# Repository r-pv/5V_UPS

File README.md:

# 5V_UPS

A real 5V Uninterruptible Power Supply (UPS) based on the [MP2637](https://www.monolithicpower.com/en/mp2637.html) IC, supporting 4.2V and 4.35V LiION/LiPO batteries. The design it's practically the design layout recomended by the manufacturer just with a few minor differences.

The board it's 30x30mm and it's capable of 2.5A battery charge and 2.4A boost output.

## Working as a proper UPS:

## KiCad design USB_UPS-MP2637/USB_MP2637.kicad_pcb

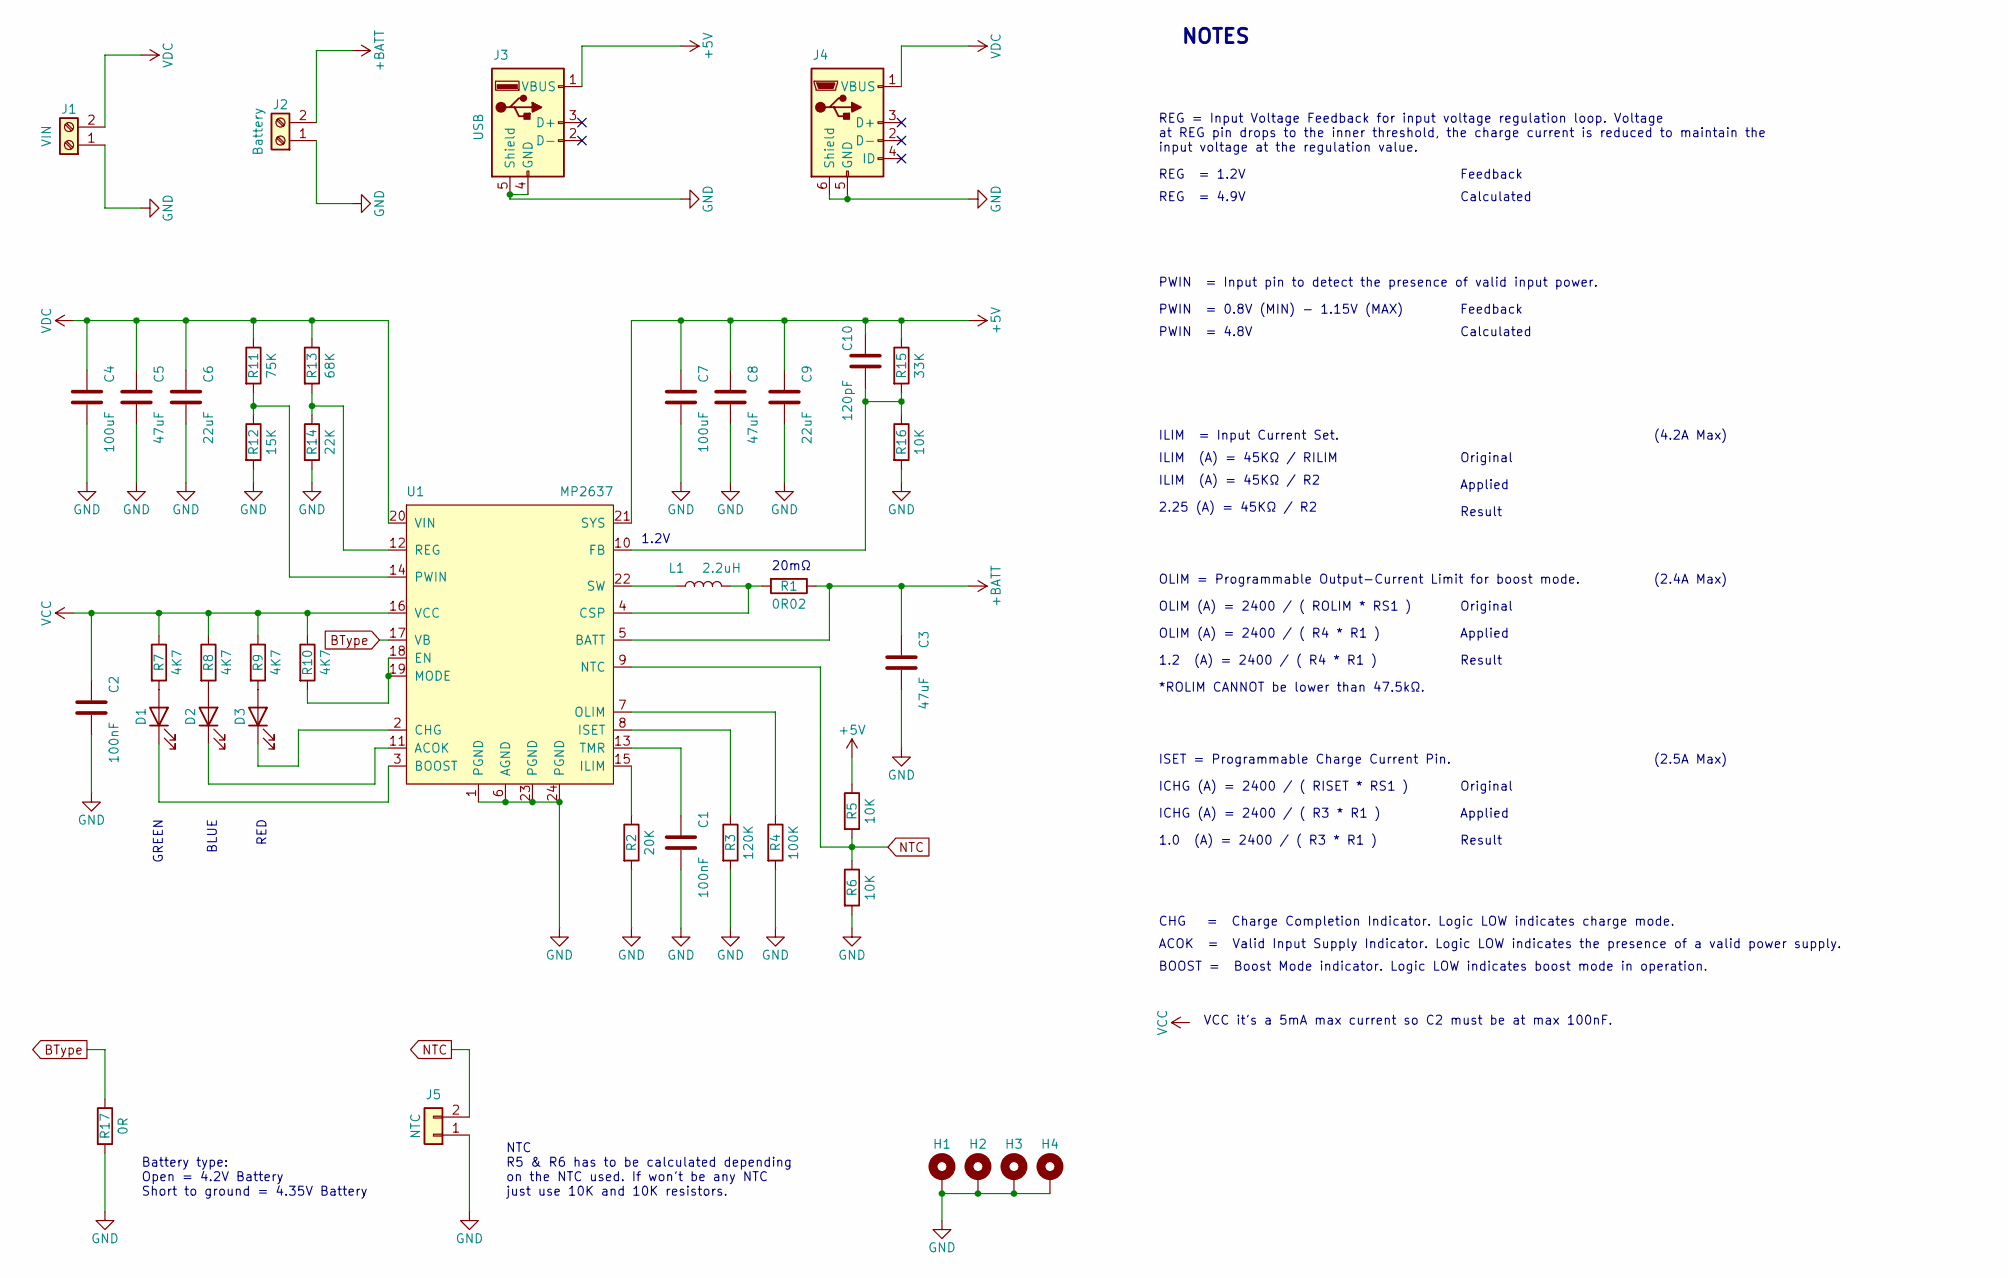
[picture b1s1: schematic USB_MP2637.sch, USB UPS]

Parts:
C1, C2: 100nF; C_0402_1005Metric
C3, C5, C8: 47uF; C_0805_2012Metric
C4, C7: 100uF; C_1210_3225Metric
C6, C9: 22uF; C_0805_2012Metric
C10: 120pF; C_0402_1005Metric
D1, D2, D3: LED_0603_1608Metric
H1, H2, H3, H4: MountingHole_2.2mm_M2_DIN965_Pad
J1: VIN; PinHeader_1x02_P2.54mm_Vertical
J2: Battery; PinHeader_1x02_P2.54mm_Vertical
J3: USB; USB_A_Molex_67643_Horizontal
J4: USB_Micro-B_Molex_47346-0001
J5: NTC; R_0805_2012Metric
L1: 2.2uH; Inductor-0603
R1: 0R02; R_1210_3225Metric
R2: 20K; R_0402_1005Metric
R3: 120K; R_0402_1005Metric
R4: 100K; R_0402_1005Metric
R5, R6, R16: 10K; R_0402_1005Metric
R7, R8, R9, R10: 4K7; R_0402_1005Metric
R11: 75K; R_0402_1005Metric
R12: 15K; R_0402_1005Metric
R13: 68K; R_0402_1005Metric
R14: 22K; R_0402_1005Metric
R15: 33K; R_0402_1005Metric
R17: 0R; R_0402_1005Metric
U1: MP2637; QFN-24_4x4mm-MP

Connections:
+5V: C7.1, C8.1, C9.1, C10.1, J3.1 (VBUS), R5.1, R15.1, U1.21 (SYS)
+BATT: C3.1, J2.2, R1.1, U1.5 (BATT)
BType: R17.1, U1.17 (VB)
GND: C1.2, C2.2, C3.2, C4.2, C5.2, C6.2, C7.2, C8.2, C9.2, H1.1, H2.1, H3.1, H4.1, J1.1, J2.1, J3.4 (GND), J3.5 (Shield), J4.5 (GND), J4.6 (Shield), J5.1, R2.2, R3.2, R4.2, R6.2, R12.2, R14.2, R16.2, R17.2, U1.1 (PGND), U1.6 (AGND), U1.23 (PGND), U1.24 (PGND)
NTC: J5.2, R5.2, R6.1, U1.9 (NTC)
unnamed: C1.1, U1.13 (TMR)
unnamed: C10.2, R15.2, R16.1, U1.10 (FB)
unnamed: D1.1 (K), U1.3 (BOOST)
unnamed: D1.2 (A), R7.2
unnamed: D2.1 (K), U1.11 (ACOK)
unnamed: D2.2 (A), R8.2
unnamed: D3.1 (K), U1.2 (CHG)
unnamed: D3.2 (A), R9.2
unnamed: L1.1, U1.22 (SW)
unnamed: L1.2, R1.2, U1.4 (CSP)
unnamed: R2.1, U1.15 (ILIM)
unnamed: R3.1, U1.8 (ISET)
unnamed: R4.1, U1.7 (OLIM)
unnamed: R10.2, U1.18 (EN), U1.19 (MODE)
unnamed: R11.2, R12.1, U1.14 (PWIN)
unnamed: R13.2, R14.1, U1.12 (REG)
VCC: C2.1, R7.1, R8.1, R9.1, R10.1, U1.16 (VCC)
VDC: C4.1, C5.1, C6.1, J1.2, J4.1 (VBUS), R11.1, R13.1, U1.20 (VIN)

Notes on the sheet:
OLIM (A) = 2400 / ( ROLIM * RS1 )
ICHG (A) = 2400 / ( RISET * RS1 )
ILIM (A) = 45KΩ / RILIM
1.2V
ILIM = Input Current Set.
OLIM = Programmable Output-Current Limit for boost mode.
ISET = Programmable Charge Current Pin.
ICHG (A) = 2400 / ( R3 * R1 )
1.0 (A) = 2400 / ( R3 * R1 )
Original
Applied
Result
OLIM (A) = 2400 / ( R4 * R1 )
1.2 (A) = 2400 / ( R4 * R1 )
ILIM (A) = 45KΩ / R2
2.25 (A) = 45KΩ / R2
REG = 1.2V
REG = Input Voltage Feedback for input voltage regulation loop. Voltage at REG pin drops to the inner threshold, the charge current is reduced to maintain the input voltage at the regulation value.
PWIN = Input pin to detect the presence of valid input power.
REG = 4.9V
Feedback
Calculated
PWIN = 0.8V (MIN) - 1.15V (MAX)
PWIN = 4.8V
*ROLIM CANNOT be lower than 47.5kΩ.
CHG = Charge Completion Indicator. Logic LOW indicates charge mode.
RED
BLUE
GREEN
ACOK = Valid Input Supply Indicator. Logic LOW indicates the presence of a valid power supply.
BOOST = Boost Mode indicator. Logic LOW indicates boost mode in operation.
NOTES
Battery type: Open = 4.2V Battery Short to ground = 4.35V Battery
(2.5A Max)
(2.4A Max)
(4.2A Max)
20mΩ
NTC R5 & R6 has to be calculated depending on the NTC used. If won't be any NTC just use 10K and 10K resistors.
VCC it's a 5mA max current so C2 must be at max 100nF.

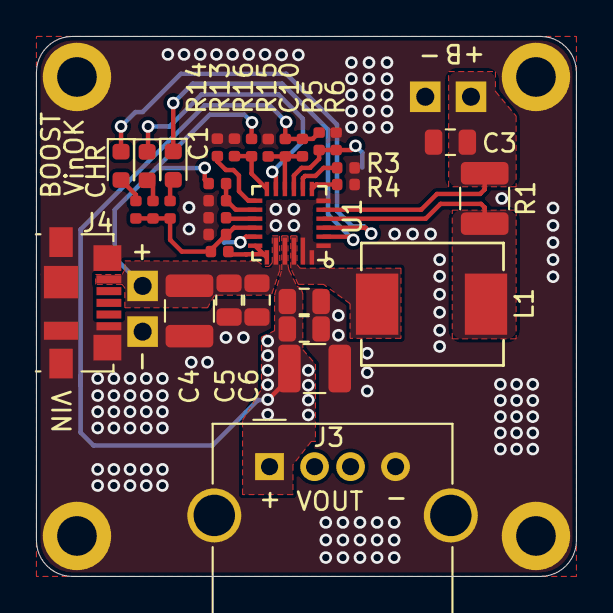
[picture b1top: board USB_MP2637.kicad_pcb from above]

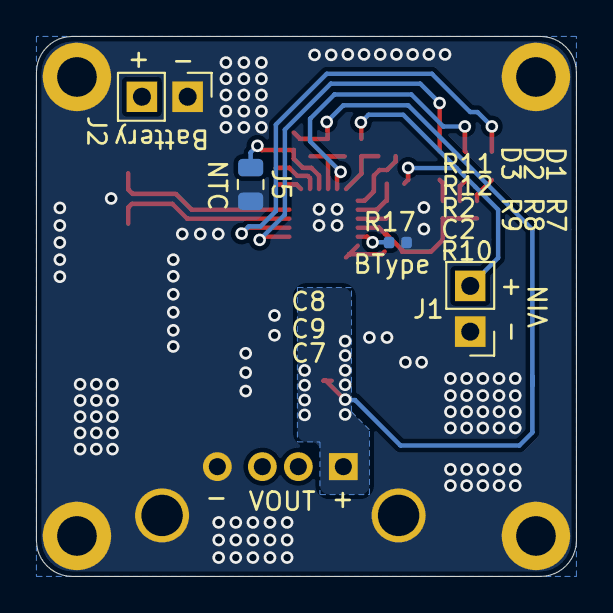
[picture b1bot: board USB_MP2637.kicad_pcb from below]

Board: 2 copper layers, 30.0 x 30.0 mm, 41 parts (4 on the bottom side), 23 nets.

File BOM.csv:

"Ref","Value","Footprint"
"C1","100nF","Capacitor_SMD:C_0402_1005Metric"
"C2","100nF","Capacitor_SMD:C_0402_1005Metric"
"C3","47uF","Capacitor_SMD:C_0805_2012Metric"
"C4","100uF","Capacitor_SMD:C_1210_3225Metric"
"C5","47uF","Capacitor_SMD:C_0805_2012Metric"
"C6","22uF","Capacitor_SMD:C_0805_2012Metric"
"C7","100uF","Capacitor_SMD:C_1210_3225Metric"
"C8","47uF","Capacitor_SMD:C_0805_2012Metric"
"C9","22uF","Capacitor_SMD:C_0805_2012Metric"
"C10","120pF","Capacitor_SMD:C_0402_1005Metric"
"D1","LED","LED_SMD:LED_0603_1608Metric"
"D2","LED","LED_SMD:LED_0603_1608Metric"
"D3","LED","LED_SMD:LED_0603_1608Metric"
"H1","Mounting Hole M2","MountingHole:MountingHole_2.2mm_M2_DIN965_Pad"
"H2","Mounting Hole M2","MountingHole:MountingHole_2.2mm_M2_DIN965_Pad"
"H3","Mounting Hole M2","MountingHole:MountingHole_2.2mm_M2_DIN965_Pad"
"H4","Mounting Hole M2","MountingHole:MountingHole_2.2mm_M2_DIN965_Pad"
"J1","VIN","Connector_PinHeader_2.54mm:PinHeader_1x02_P2.54mm_Vertical"
"J2","Battery","Connector_PinHeader_2.54mm:PinHeader_1x02_P2.54mm_Vertical"
"J3","USB_OUT","Connector_USB:USB_A_Molex_67643_Horizontal"
"J4","USB_IN","Connector_USB:USB_Micro-B_Molex_47346-0001"
"J5","NTC","Resistor_SMD:R_0805_2012Metric"
"L1","2.2uH",".rpvM:Inductor-0603"
"R1","0R02","Resistor_SMD:R_1210_3225Metric"
"R2","20K","Resistor_SMD:R_0402_1005Metric"
"R3","120K","Resistor_SMD:R_0402_1005Metric"
"R4","100K","Resistor_SMD:R_0402_1005Metric"
"R5","10K","Resistor_SMD:R_0402_1005Metric"
"R6","10K","Resistor_SMD:R_0402_1005Metric"
"R7","4K7","Resistor_SMD:R_0402_1005Metric"
"R8","4K7","Resistor_SMD:R_0402_1005Metric"
"R9","4K7","Resistor_SMD:R_0402_1005Metric"
"R10","4K7","Resistor_SMD:R_0402_1005Metric"
"R11","75K","Resistor_SMD:R_0402_1005Metric"
"R12","15K","Resistor_SMD:R_0402_1005Metric"
"R13","68K","Resistor_SMD:R_0402_1005Metric"
"R14","22K","Resistor_SMD:R_0402_1005Metric"
"R15","33K","Resistor_SMD:R_0402_1005Metric"
"R16","10K","Resistor_SMD:R_0402_1005Metric"
"R17","0R","Resistor_SMD:R_0402_1005Metric"
"U1","MP2637","QFN-24_4x4mm-MP"

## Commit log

2020-12-14 5V_UPS
